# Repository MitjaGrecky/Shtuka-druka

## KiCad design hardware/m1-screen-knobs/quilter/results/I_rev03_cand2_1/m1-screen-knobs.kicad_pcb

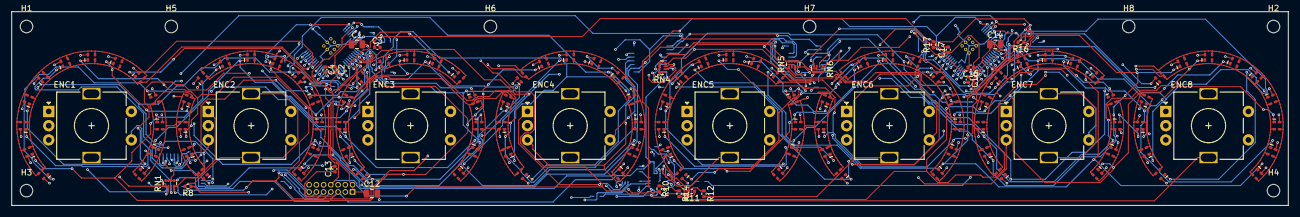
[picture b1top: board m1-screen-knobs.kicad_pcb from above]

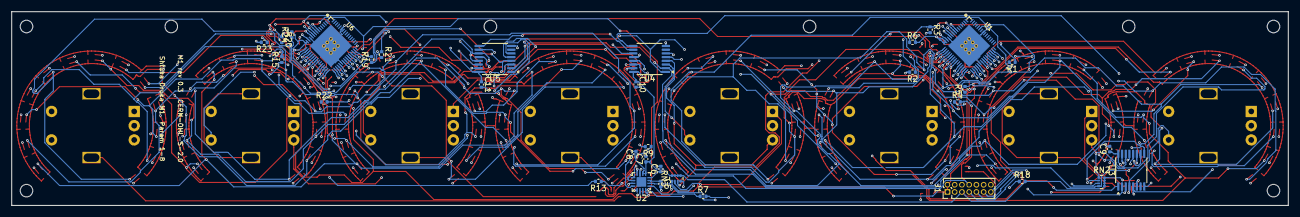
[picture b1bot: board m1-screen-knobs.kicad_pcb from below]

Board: 4 copper layers, 224.0 x 34.0 mm, 174 parts (33 on the bottom side), 114 nets.

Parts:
C1, C14: 4.7u; C_0805_2012Metric
C2, C7, C13, C15: 1u; C_0402_1005Metric
C3, C4, C6, C8, C9, C10, C11, C16, C17: 100n; C_0402_1005Metric
C5: 2.2n; C_0402_1005Metric
C12: 10u; C_0805_2012Metric
D1, D2, D3, D4, D5, D6, D7, D8, D9, D10, D11, D12, D13, D14, D15, D16, D17, D18, D19, D20, D21, D22, D23, D24, D25, D26, D27, D28, D29, D30, D31, D32, D33, D34, D35, D36, D37, D38, D39, D40, D41, D42, D43, D44, D45, D46, D47, D48, D49, D50, D51, D52, D53, D54, D55, D56, D57, D58, D59, D60, D61, D62, D63, D64, D65, D66, D67, D68, D69, D70, D71, D72, D73, D74, D75, D76, D77, D78, D79, D80, D81, D82, D83, D84, D85, D86, D87, D88, D89, D90, D91, D92, D93, D94, D95, D96, D97, D98, D99, D100, D101, D102, D103, D104: XL-1615RGBC-RF; LED_RGB_XL-1615RGBC_1.6x1.5mm
ENC1, ENC2, ENC3, ENC4, ENC5, ENC6, ENC7, ENC8: EC11E smooth, switch; RotaryEncoder_Alps_EC11E-Switch_Vertical_H20mm_Ring
H1, H2, H3, H4, H5, H6, H7, H8: M2; MountingHole_2.2mm_M2
J1: Module bus 2x7 1.27; PinHeader_2x07_P1.27mm_Vertical
R1, R19: 20k 1%; R_0402_1005Metric
R2, R17, R18, R20: 10k; R_0402_1005Metric
R3, R4, R5, R6, R21, R22, R23, R24: 0; R_0402_1005Metric
R7, R8, R9, R10, R11, R12, R13, R14: 560; R_0402_1005Metric
R15, R16: 4.7k; R_0402_1005Metric
RN1, RN2, RN3, RN4, RN5, RN6: 4x10k; R_Array_Convex_4x0402
U1, U6: IS31FL3741A-QFLS4-TR; QFN-60-1EP_7x7mm_P0.4mm_EP5.25x5.25mm
U2: CY8CMBR3108-LQXIT; QFN-16-1EP_3x3mm_P0.5mm_EP1.7x1.7mm
U3, U4, U5: 74HC165PW; TSSOP-16_4.4x5mm_P0.65mm

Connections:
+3V3: C7.1, C8.1, C9.1, C10.1, C11.1, C13.1, J1.5, R2.2, R15.2, R16.2, R17.2, R18.2, R20.2, RN1.5, RN1.6, RN1.7, RN1.8, RN2.5, RN2.6, RN2.7, RN2.8, RN3.5, RN3.6, RN3.7, RN3.8, RN4.5, RN4.6, RN4.7, RN4.8, RN5.5, RN5.6, RN5.7, RN5.8, RN6.5, RN6.6, RN6.7, RN6.8, U2.5, U2.6, U3.16, U4.16, U5.16
+5V: C1.1, C2.1, C3.1, C4.1, C12.1, C14.1, C15.1, C16.1, C17.1, J1.1, J1.2, R6.2, R24.2, U1.14, U1.15, U1.25, U6.14, U6.15, U6.25
/A_ADDR: R3.1, R4.1, R5.1, R6.1, U1.8
/A_CS1: D27.1, D28.1, D29.1, D30.1, D31.1, D32.1, D33.1, D34.1, D35.1, U1.26
/A_CS2: D27.3, D28.3, D29.3, D30.3, D31.3, D32.3, D33.3, D34.3, D35.3, U1.27
/A_CS3: D27.4, D28.4, D29.4, D30.4, D31.4, D32.4, D33.4, D34.4, D35.4, U1.28
/A_CS4: D44.1, D45.1, D46.1, D47.1, D48.1, D49.1, D50.1, D51.1, D52.1, U1.29
/A_CS5: D44.3, D45.3, D46.3, D47.3, D48.3, D49.3, D50.3, D51.3, D52.3, U1.30
/A_CS6: D44.4, D45.4, D46.4, D47.4, D48.4, D49.4, D50.4, D51.4, D52.4, U1.31
/A_CS7: D36.1, D37.1, D38.1, D39.1, D40.1, D41.1, D42.1, D43.1, U1.32
/A_CS8: D36.3, D37.3, D38.3, D39.3, D40.3, D41.3, D42.3, D43.3, U1.33
/A_CS9: D36.4, D37.4, D38.4, D39.4, D40.4, D41.4, D42.4, D43.4, U1.34
/A_CS10: D1.1, D2.1, D3.1, D4.1, D5.1, D6.1, D7.1, D8.1, D9.1, U1.35
/A_CS11: D1.3, D2.3, D3.3, D4.3, D5.3, D6.3, D7.3, D8.3, D9.3, U1.37
/A_CS12: D1.4, D2.4, D3.4, D4.4, D5.4, D6.4, D7.4, D8.4, D9.4, U1.38
/A_CS13: D18.1, D19.1, D20.1, D21.1, D22.1, D23.1, D24.1, D25.1, D26.1, U1.39
/A_CS14: D18.3, D19.3, D20.3, D21.3, D22.3, D23.3, D24.3, D25.3, D26.3, U1.40
/A_CS15: D18.4, D19.4, D20.4, D21.4, D22.4, D23.4, D24.4, D25.4, D26.4, U1.41
/A_CS16: D10.1, D11.1, D12.1, D13.1, D14.1, D15.1, D16.1, D17.1, U1.42
/A_CS17: D10.3, D11.3, D12.3, D13.3, D14.3, D15.3, D16.3, D17.3, U1.43
/A_CS18: D10.4, D11.4, D12.4, D13.4, D14.4, D15.4, D16.4, D17.4, U1.44
/A_REXT: R1.1, U1.13
/A_SDB: R2.1, U1.11
/A_SW1: D1.2, D10.2, D18.2, D27.2, D36.2, D44.2, U1.16
/A_SW2: D2.2, D11.2, D19.2, D28.2, D37.2, D45.2, U1.17
/A_SW3: D3.2, D12.2, D20.2, D29.2, D38.2, D46.2, U1.18
/A_SW4: D4.2, D13.2, D21.2, D30.2, D39.2, D47.2, U1.19
/A_SW5: D5.2, D14.2, D22.2, D31.2, D40.2, D48.2, U1.20
/A_SW6: D6.2, D15.2, D23.2, D32.2, D41.2, D49.2, U1.21
/A_SW7: D7.2, D16.2, D24.2, D33.2, D42.2, D50.2, U1.22
/A_SW8: D8.2, D17.2, D25.2, D34.2, D43.2, D51.2, U1.23
/A_SW9: D9.2, D26.2, D35.2, D52.2, U1.24
/B_ADDR: R21.1, R22.1, R23.1, R24.1, U6.8
/B_CS1: D79.1, D80.1, D81.1, D82.1, D83.1, D84.1, D85.1, D86.1, D87.1, U6.26
/B_CS2: D79.3, D80.3, D81.3, D82.3, D83.3, D84.3, D85.3, D86.3, D87.3, U6.27
/B_CS3: D79.4, D80.4, D81.4, D82.4, D83.4, D84.4, D85.4, D86.4, D87.4, U6.28
/B_CS4: D96.1, D97.1, D98.1, D99.1, D100.1, D101.1, D102.1, D103.1, D104.1, U6.29
/B_CS5: D96.3, D97.3, D98.3, D99.3, D100.3, D101.3, D102.3, D103.3, D104.3, U6.30
/B_CS6: D96.4, D97.4, D98.4, D99.4, D100.4, D101.4, D102.4, D103.4, D104.4, U6.31
/B_CS7: D88.1, D89.1, D90.1, D91.1, D92.1, D93.1, D94.1, D95.1, U6.32
/B_CS8: D88.3, D89.3, D90.3, D91.3, D92.3, D93.3, D94.3, D95.3, U6.33
/B_CS9: D88.4, D89.4, D90.4, D91.4, D92.4, D93.4, D94.4, D95.4, U6.34
/B_CS10: D53.1, D54.1, D55.1, D56.1, D57.1, D58.1, D59.1, D60.1, D61.1, U6.35
/B_CS11: D53.3, D54.3, D55.3, D56.3, D57.3, D58.3, D59.3, D60.3, D61.3, U6.37
/B_CS12: D53.4, D54.4, D55.4, D56.4, D57.4, D58.4, D59.4, D60.4, D61.4, U6.38
/B_CS13: D70.1, D71.1, D72.1, D73.1, D74.1, D75.1, D76.1, D77.1, D78.1, U6.39
/B_CS14: D70.3, D71.3, D72.3, D73.3, D74.3, D75.3, D76.3, D77.3, D78.3, U6.40
/B_CS15: D70.4, D71.4, D72.4, D73.4, D74.4, D75.4, D76.4, D77.4, D78.4, U6.41
/B_CS16: D62.1, D63.1, D64.1, D65.1, D66.1, D67.1, D68.1, D69.1, U6.42
/B_CS17: D62.3, D63.3, D64.3, D65.3, D66.3, D67.3, D68.3, D69.3, U6.43
/B_CS18: D62.4, D63.4, D64.4, D65.4, D66.4, D67.4, D68.4, D69.4, U6.44
/B_REXT: R19.1, U6.13
/B_SDB: R20.1, U6.11
/B_SW1: D53.2, D62.2, D70.2, D79.2, D88.2, D96.2, U6.16
/B_SW2: D54.2, D63.2, D71.2, D80.2, D89.2, D97.2, U6.17
/B_SW3: D55.2, D64.2, D72.2, D81.2, D90.2, D98.2, U6.18
/B_SW4: D56.2, D65.2, D73.2, D82.2, D91.2, D99.2, U6.19
/B_SW5: D57.2, D66.2, D74.2, D83.2, D92.2, D100.2, U6.20
/B_SW6: D58.2, D67.2, D75.2, D84.2, D93.2, D101.2, U6.21
/B_SW7: D59.2, D68.2, D76.2, D85.2, D94.2, D102.2, U6.22
/B_SW8: D60.2, D69.2, D77.2, D86.2, D95.2, D103.2, U6.23
/B_SW9: D61.2, D78.2, D87.2, D104.2, U6.24
/CMOD: C5.1, U2.3
/E0_A: ENC1.A, RN1.1, U3.6
/E0_B: ENC1.B, RN1.2, U3.5
/E0_SW: ENC1.S1, RN1.3, U3.4
/E1_A: ENC2.A, RN1.4, U3.3
/E1_B: ENC2.B, RN2.1, U3.14
/E1_SW: ENC2.S1, RN2.2, U3.13
/E2_A: ENC3.A, RN2.3, U3.12
/E2_B: ENC3.B, RN2.4, U3.11
/E2_SW: ENC3.S1, RN3.1, U4.6
/E3_A: ENC4.A, RN3.2, U4.5
/E3_B: ENC4.B, RN3.3, U4.4
/E3_SW: ENC4.S1, RN3.4, U4.3
/E4_A: ENC5.A, RN4.1, U4.14
/E4_B: ENC5.B, RN4.2, U4.13
/E4_SW: ENC5.S1, RN4.3, U4.12
/E5_A: ENC6.A, RN4.4, U4.11
/E5_B: ENC6.B, RN5.1, U5.6
/E5_SW: ENC6.S1, RN5.2, U5.5
/E6_A: ENC7.A, RN5.3, U5.4
/E6_B: ENC7.B, RN5.4, U5.3
/E6_SW: ENC7.S1, RN6.1, U5.14
/E7_A: ENC8.A, RN6.2, U5.13
/E7_B: ENC8.B, RN6.3, U5.12
/E7_SW: ENC8.S1, RN6.4, U5.11
/SCL: J1.8, R4.2, R16.1, R22.2, U1.10, U2.15, U6.10
/SDA: J1.7, R5.2, R15.1, R23.2, U1.9, U2.14, U6.9
/SR_CLK: J1.12, U3.2, U4.2, U5.2
/SR_IN: J1.14, R18.1, U5.10
/SR_OUT: J1.13, U3.9
/SR_Q3: U3.10, U4.9
/SR_Q4: U4.10, U5.9
/TOUCH0: ENC1.MP, R7.2
/TOUCH1: ENC2.MP, R8.2
/TOUCH2: ENC3.MP, R9.2
/TOUCH3: ENC4.MP, R10.2
/TOUCH4: ENC5.MP, R11.2
/TOUCH5: ENC6.MP, R12.2
/TOUCH6: ENC7.MP, R13.2
/TOUCH7: ENC8.MP, R14.2
/TR0: R7.1, U2.1
/TR1: R8.1, U2.2
/TR2: R9.1, U2.12
/TR3: R10.1, U2.13
/TR4: R11.1, U2.8
/TR5: R12.1, U2.9
/TR6: R13.1, U2.10
/TR7: R14.1, U2.11
/VREG: C6.1, U2.4
/~INT: J1.9, R17.1, U1.7, U2.16, U6.7
/~SR_LOAD: J1.11, U3.1, U4.1, U5.1
GND: C1.2, C2.2, C3.2, C4.2, C5.2, C6.2, C7.2, C8.2, C9.2, C10.2, C11.2, C12.2, C13.2, C14.2, C15.2, C16.2, C17.2, ENC1.C, ENC1.S2, ENC2.C, ENC2.S2, ENC3.C, ENC3.S2, ENC4.C, ENC4.S2, ENC5.C, ENC5.S2, ENC6.C, ENC6.S2, ENC7.C, ENC7.S2, ENC8.C, ENC8.S2, J1.3, J1.4, J1.6, J1.10, R1.2, R3.2, R19.2, R21.2, U1.12, U1.36, U1.55, U1.61, U2.7, U2.17, U3.8, U3.15, U4.8, U4.15, U5.8, U5.15, U6.12, U6.36, U6.55, U6.61

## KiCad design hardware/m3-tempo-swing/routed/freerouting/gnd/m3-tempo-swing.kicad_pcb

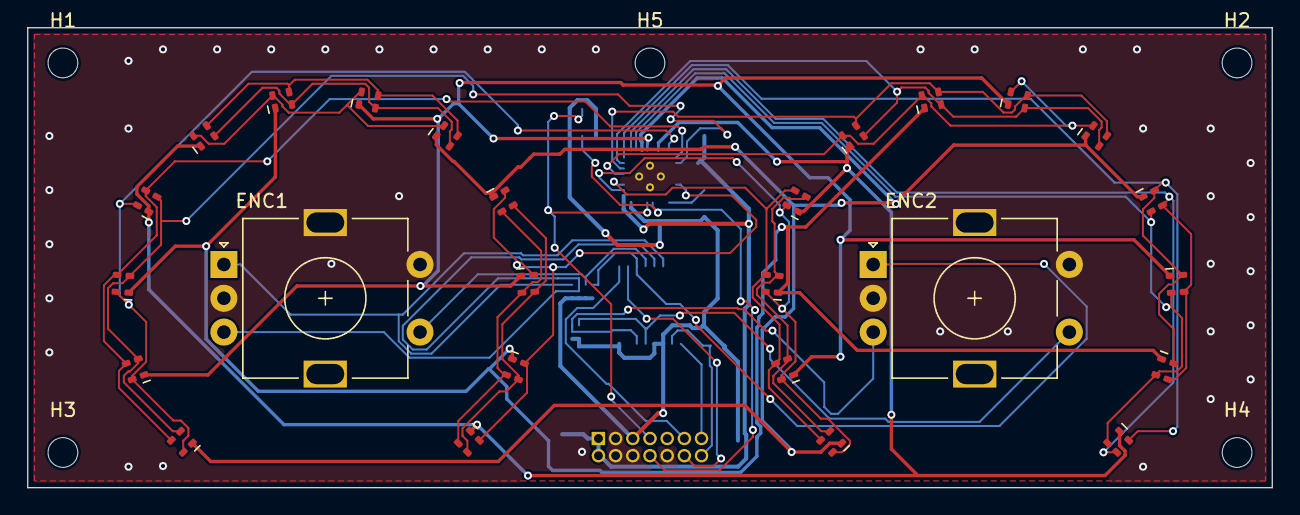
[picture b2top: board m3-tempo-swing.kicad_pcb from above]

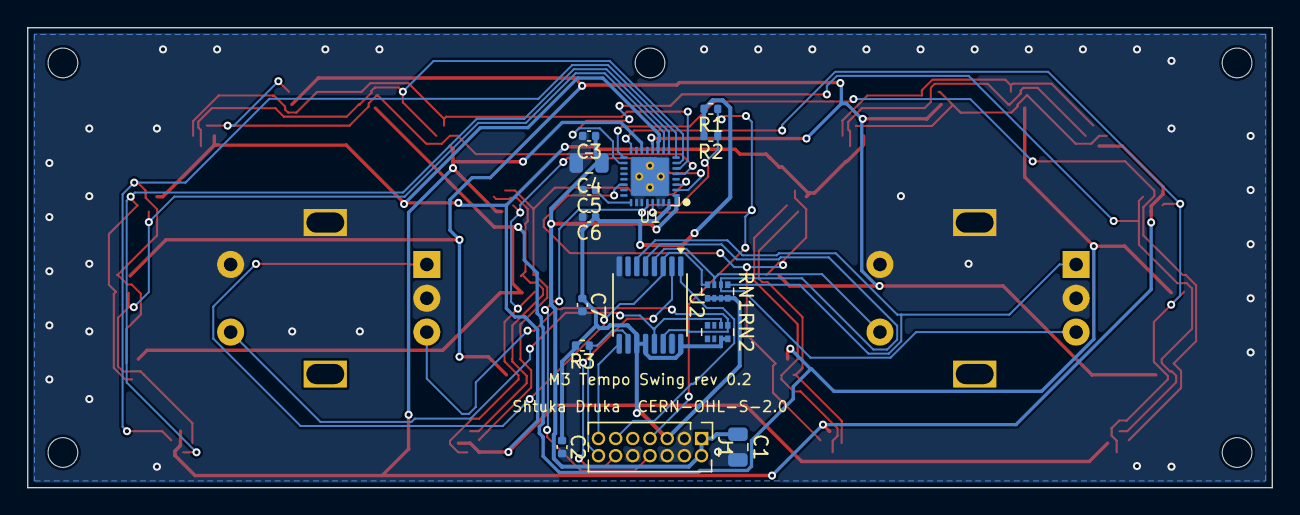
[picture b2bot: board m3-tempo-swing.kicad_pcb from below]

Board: 2 copper layers, 92.0 x 34.0 mm, 46 parts (15 on the bottom side), 38 nets.

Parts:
C1: 10u; C_0805_2012Metric
C2, C3, C5: 1u; C_0402_1005Metric
C4: 4.7u; C_0805_2012Metric
C6: 1n; C_0402_1005Metric
C7: 100n; C_0402_1005Metric
D1, D2, D3, D4, D5, D6, D7, D8, D9, D10, D11, D12, D13, D14, D15, D16, D17, D18, D19, D20, D21, D22, D23, D24: XL-1615RGBC-RF; LED_RGB_XL-1615RGBC_1.6x1.5mm
ENC1, ENC2: EC11E smooth, switch; RotaryEncoder_Alps_EC11E-Switch_Vertical_H20mm_Ring
H1, H2, H3, H4, H5: M2; MountingHole_2.2mm_M2
J1: Module bus 2x7 1.27; PinHeader_2x07_P1.27mm_Vertical
R1, R2: 4.7k; R_0402_1005Metric
R3: 10k; R_0402_1005Metric
RN1, RN2: 4x10k; R_Array_Convex_4x0402
U1: LP5864RSMR; VQFN-32-1EP_4x4mm_P0.4mm_EP2.8x2.8mm
U2: 74HC165PW; TSSOP-16_4.4x5mm_P0.65mm

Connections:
+3V3: C2.1, C6.1, C7.1, J1.5, R1.2, R2.2, R3.2, RN1.5, RN1.6, RN1.7, RN1.8, RN2.7, RN2.8, U1.32, U2.11, U2.12, U2.16
+5V: C1.1, C3.1, C4.1, J1.1, J1.2, U1.1, U1.15
/A_CS0: D13.1, D14.1, D15.1, D16.1, U1.2
/A_CS1: D13.3, D14.3, D15.3, D16.3, U1.3
/A_CS2: D13.4, D14.4, D15.4, D16.4, U1.4
/A_CS3: D17.1, D18.1, D19.1, D20.1, U1.5
/A_CS4: D17.3, D18.3, D19.3, D20.3, U1.6
/A_CS5: D17.4, D18.4, D19.4, D20.4, U1.7
/A_CS6: D21.1, D22.1, D23.1, D24.1, U1.8
/A_CS7: D21.3, D22.3, D23.3, D24.3, U1.9
/A_CS8: D21.4, D22.4, D23.4, D24.4, U1.10
/A_CS9: D1.1, D2.1, D3.1, D4.1, U1.16
/A_CS10: D1.3, D2.3, D3.3, D4.3, U1.17
/A_CS11: D1.4, D2.4, D3.4, D4.4, U1.18
/A_CS12: D5.1, D6.1, D7.1, D8.1, U1.19
/A_CS13: D5.3, D6.3, D7.3, D8.3, U1.20
/A_CS14: D5.4, D6.4, D7.4, D8.4, U1.21
/A_CS15: D9.1, D10.1, D11.1, D12.1, U1.22
/A_CS16: D9.3, D10.3, D11.3, D12.3, U1.23
/A_CS17: D9.4, D10.4, D11.4, D12.4, U1.24
/A_SW0: D1.2, D8.2, D9.2, D13.2, D20.2, D21.2, U1.11
/A_SW1: D2.2, D7.2, D10.2, D14.2, D19.2, D22.2, U1.12
/A_SW2: D3.2, D6.2, D11.2, D15.2, D18.2, D23.2, U1.13
/A_SW3: D4.2, D5.2, D12.2, D16.2, D17.2, D24.2, U1.14
/A_VCAP: C5.1, U1.25
/E0_A: ENC1.A, RN1.1, U2.6
/E0_B: ENC1.B, RN1.2, U2.5
/E0_SW: ENC1.S1, RN1.3, U2.4
/E1_A: ENC2.A, RN1.4, U2.3
/E1_B: ENC2.B, RN2.1, U2.14
/E1_SW: ENC2.S1, RN2.2, U2.13
/SCL: J1.8, R2.1, U1.28
/SDA: J1.7, R1.1, U1.29
/SR_CLK: J1.12, U2.2
/SR_IN: J1.14, R3.1, U2.10
/SR_OUT: J1.13, U2.9
/~SR_LOAD: J1.11, U2.1
GND: C1.2, C2.2, C3.2, C4.2, C5.2, C6.2, C7.2, ENC1.C, ENC1.MP, ENC1.S2, ENC2.C, ENC2.MP, ENC2.S2, J1.3, J1.4, J1.6, J1.10, U1.26, U1.27, U1.30, U1.31, U1.33, U2.8, U2.15

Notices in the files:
hardware/m1-screen-knobs/quilter/results/I_rev03_cand2_1/m1-screen-knobs.kicad_pcb:
Shtuka Druka - open hardware, CERN-OHL-S-2.0
M1 rev 0.3  CERN-OHL-S-2.0
hardware/m3-tempo-swing/routed/freerouting/gnd/m3-tempo-swing.kicad_pcb:
Shtuka Druka  CERN-OHL-S-2.0
